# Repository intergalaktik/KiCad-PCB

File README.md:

# KiCad-PCB
Template for KiCad PCB with actions addon

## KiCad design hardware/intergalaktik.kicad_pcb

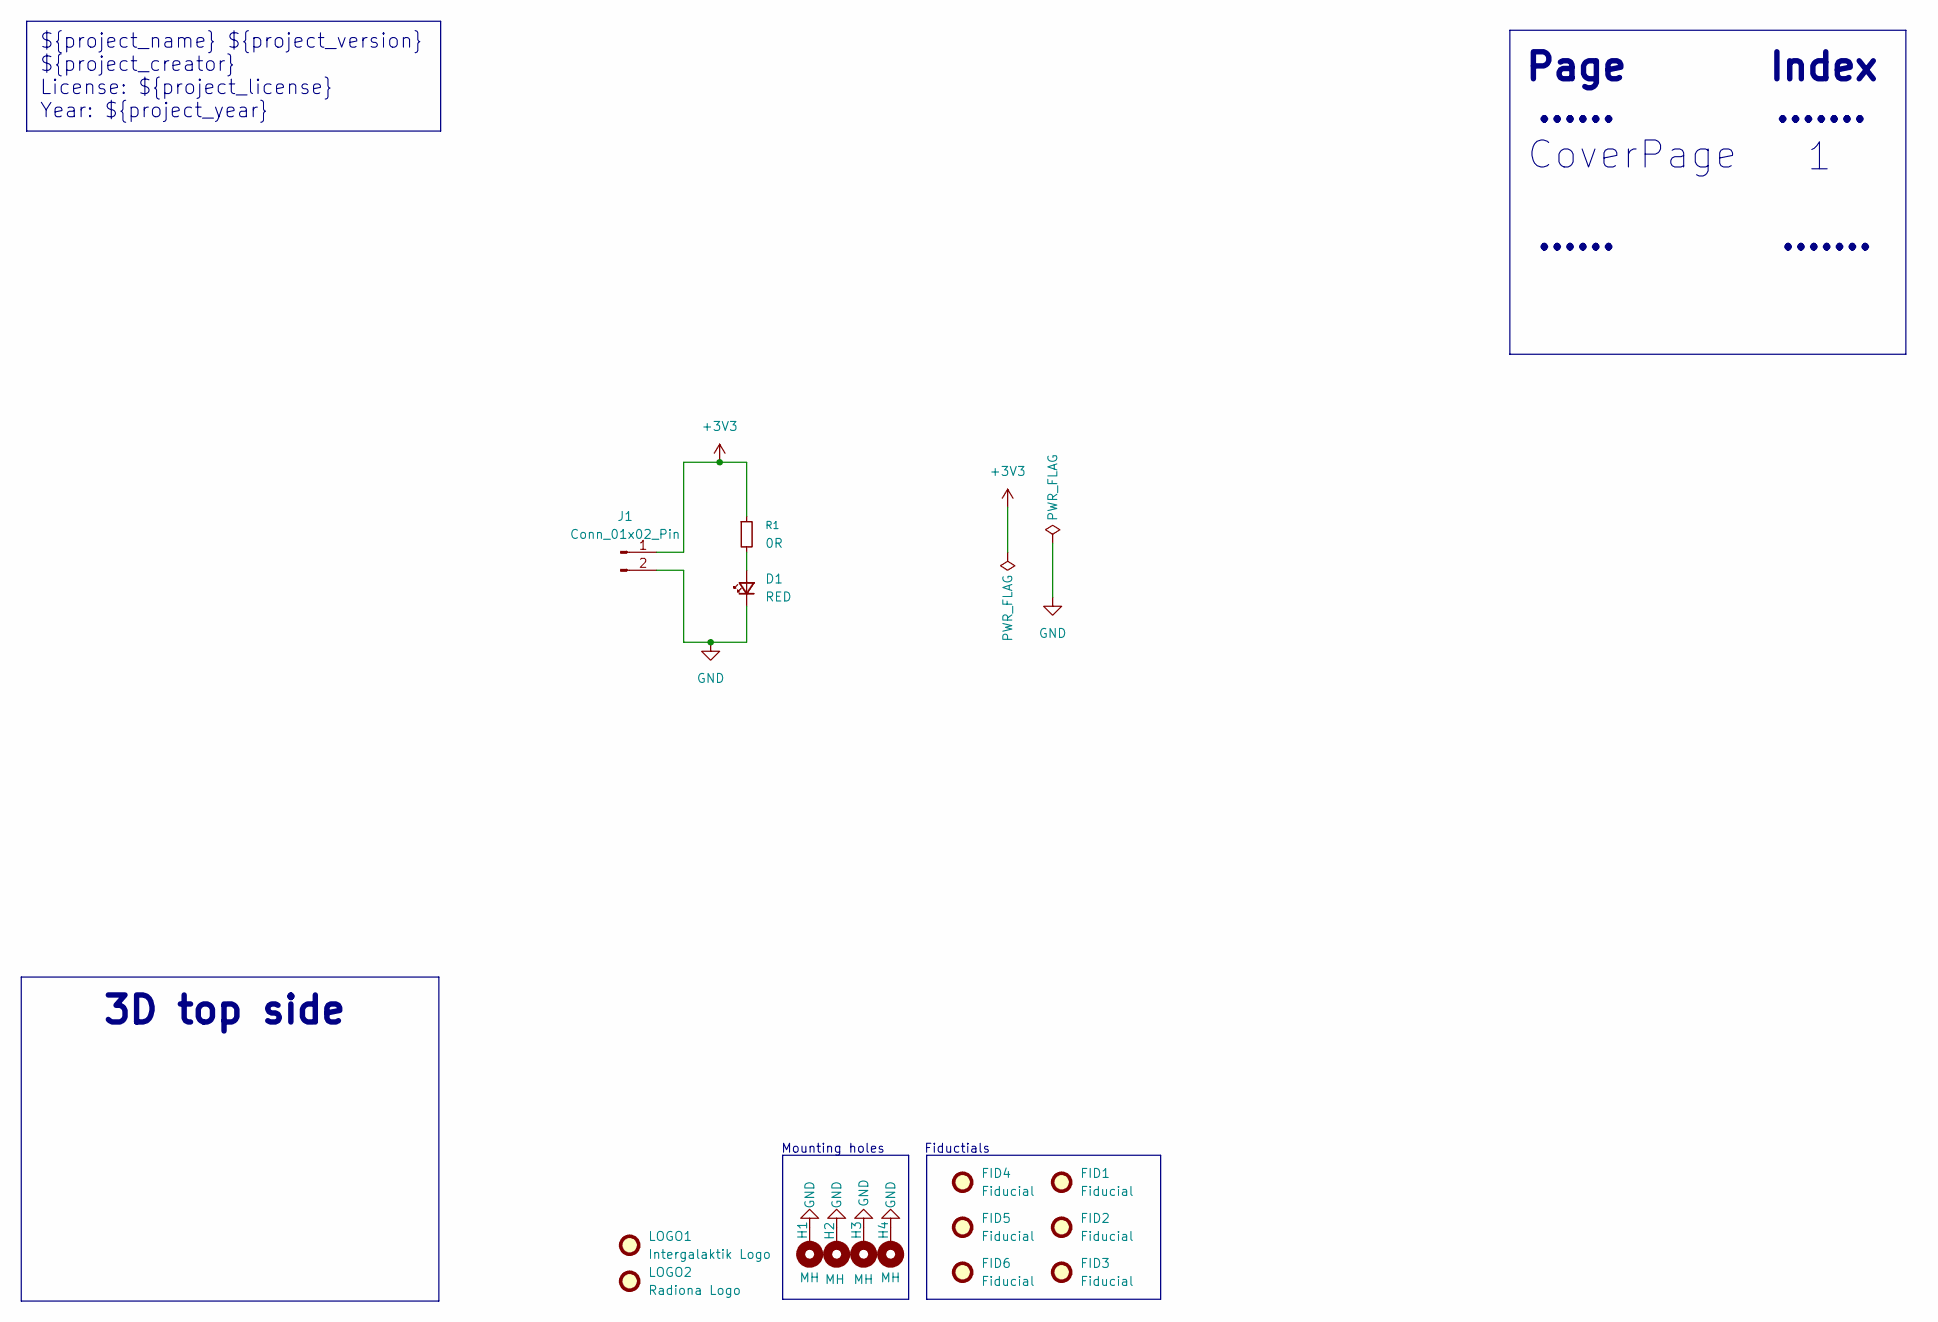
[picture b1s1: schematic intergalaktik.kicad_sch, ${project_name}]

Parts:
D1: RED; LED_0603_1608Metric; LCSC C965799
FID1, FID2, FID3, FID4, FID5, FID6: Fiducial; Fiducial_0.5mm_Mask1mm
H1, H2, H3, H4: MH; MountingHole_3mm_Pad
J1: Conn_01x02_Pin; PinHeader_1x02_P2.54mm_Vertical; LCSC C18077872
LOGO1: Intergalaktik Logo; intergalaktik
LOGO2: Radiona Logo; radiona
R1: 0R; C_0402_1005Metric; LCSC C106231

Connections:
+3V3: J1.1, R1.1
GND: D1.1 (K), H1.1, H2.1, H3.1, H4.1, J1.2
unnamed: D1.2 (A), R1.2

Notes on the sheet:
Fiductials
3D top side
......
CoverPage
${project_name} ${project_version} ${project_creator} License: ${project_license} Year: ${project_year}
Page
Mounting holes
.......
Index

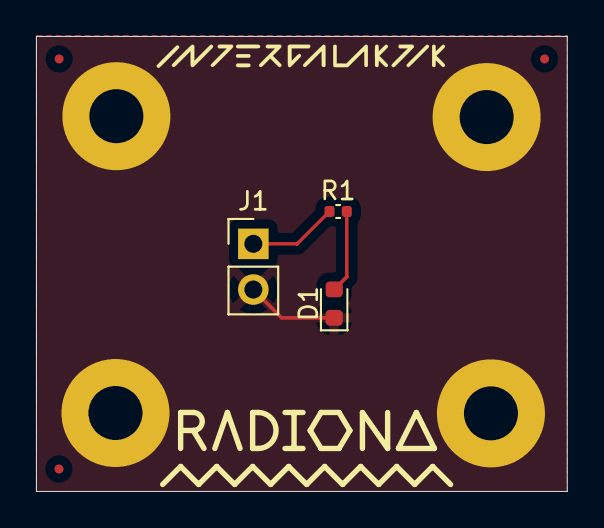
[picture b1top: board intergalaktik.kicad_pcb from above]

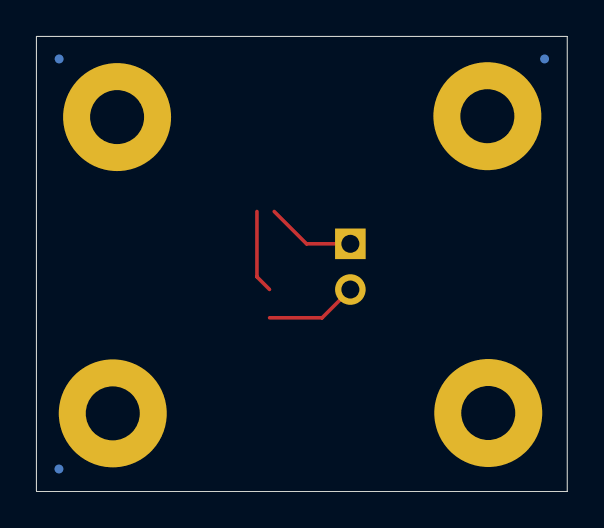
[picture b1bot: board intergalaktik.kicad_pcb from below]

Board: 4 copper layers, 29.5 x 25.3 mm, 15 parts (3 on the bottom side), 3 nets.

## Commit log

2025-11-07 Adding actions
2025-11-07 Adding KiCad files
2025-11-07 Updating action
2025-11-07 fixing path
2025-11-07 updating to KiCad 9
2025-11-07 updating KiBot to dev
2025-11-07 Update production files [skip ci]
2025-11-07 install zip
2025-11-07 adding tag to begining
2025-11-07 remove zip
2025-11-07 Adding files directly
2025-11-07 Change tag to JLCPCB - adding more files
2025-11-07 Removing old production folder

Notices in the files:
parts and their libraries:
project_license: CERN-OHL-S v2
